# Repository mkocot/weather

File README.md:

# Known ID
0x00 Reserved
0x01 Temerature
0x02 Pressure
0x03 Humidity
0x04 UNUSED (was time)
0x05 Voltage (like in battery power)
0x06 Screen

Packet
name    value   size    note
MAGIC   W       1
Version 1       1
MAC     ?       6
Count   ?       1       Total number of 'sensors' in Packet
Payload ?       ?
Sensor
ID      ?       1       See Known ID
DATA

Most sensors use 4 bytes of data

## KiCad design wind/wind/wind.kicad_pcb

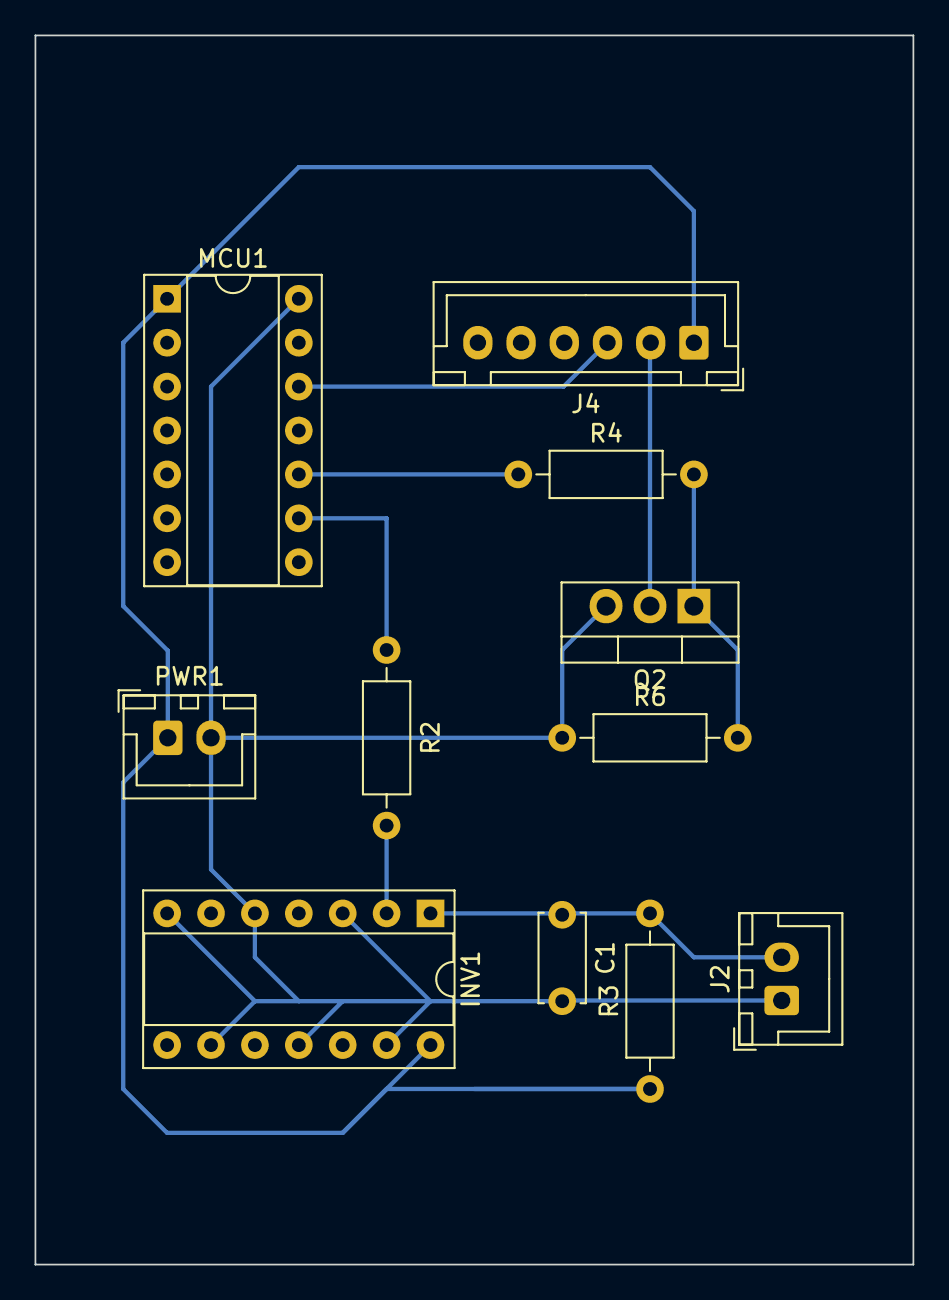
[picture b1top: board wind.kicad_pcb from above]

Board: 2 copper layers, 50.8 x 71.1 mm, 11 parts (0 on the bottom side), 9 nets.

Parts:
C1: 100n; C_Disc_D5.0mm_W2.5mm_P5.00mm
INV1: 74HC14; DIP-14_W7.62mm_Socket
J2: Conn_01x02_Socket; JST_XH_B2B-XH-A_1x02_P2.50mm_Vertical
J4: Conn_01x05_Socket; JST_XH_B6B-XH-A_1x06_P2.50mm_Vertical
MCU1: ATtiny24-20P; DIP-14_W7.62mm_Socket
PWR1: Conn_01x02_Socket; JST_XH_B2B-XH-A_1x02_P2.50mm_Vertical
Q2: IRLZ44N; TO-220-3_Vertical
R2: 1k; R_Axial_DIN0207_L6.3mm_D2.5mm_P10.16mm_Horizontal
R3: 47K; R_Axial_DIN0207_L6.3mm_D2.5mm_P10.16mm_Horizontal
R4: 10k; R_Axial_DIN0207_L6.3mm_D2.5mm_P10.16mm_Horizontal
R6: 56K; R_Axial_DIN0207_L6.3mm_D2.5mm_P10.16mm_Horizontal

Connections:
+3V3: INV1.14 (VCC), J4.1, MCU1.1 (VCC), PWR1.1, R3.1
/RadioController/GND_IN: J4.2, Q2.2 (D)
/RadioController/RADIO_EN: MCU1.10 (PA3), R4.1
/RadioController/Rx: J4.3, MCU1.12 (PA1)
GND: C1.2, INV1.3, INV1.5, INV1.7 (GND), INV1.9, INV1.11, INV1.13, J2.1, MCU1.14 (GND), PWR1.2, Q2.3 (S), R6.1
unnamed: INV1.2, R2.2
unnamed: C1.1, INV1.1, J2.2, R3.2
unnamed: MCU1.9 (PA4), R2.1
unnamed: Q2.1 (G), R4.2, R6.2

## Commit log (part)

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2021-01-13 init
2021-01-13 ignore config.h
2021-01-13 Change source file name
2021-01-16 Add web backend
2021-01-16 Fix (badly) 12h format to 24h
2021-01-18 reformat
2021-01-18 remove unused import
2021-01-18 add server side
2021-01-18 Add auto refresh
2021-01-18 Change default server port
2021-01-18 Add example systemd services
2021-01-20 remove not used code
2021-02-04 Get latest not earliest date
2021-02-08 Filter-out outilers
2021-03-13 Add known id to readme
2021-03-13 Remove unused parsts
2021-03-13 Add more info
2021-03-15 working prototype
2021-03-18 overhaul
2021-03-18 add font
2021-03-18 Dang, we need old python3
2021-03-18 make it old again
2021-03-18 another fixes
2021-03-18 minor fixes
2021-03-18 Fix: invalid device id
2021-03-18 add missing font data
2021-03-18 fix graph
2021-03-18 add draw module...
2021-03-18 quick and dirty server fix
2021-04-12 Weather: Battery optimization
    + Assigned static IP (255.255.255.255/32) rfc6890
    + Disable Serial by default (W_SILENT flag)
    + Disable LED by default (W_BLINK) - it will 'blink' on start anyway,
    this is somehow hardwired
    + UDP: use yield() not delay(2000) after endPacket
    + Add delay after deepSleep ensuring we don't hit loop again
2021-04-12 weather: Change IP
    + Replace 255.255.255.255 with 127.255.255.255. Previous one was causing some odd issues. This address is set only to prevent DHCP requests.
    + Add small delay after yield in UDP, as sometimes packets was not
    received
2021-04-13 Increase delay after finishing UDP to 300ms
    When signal is weak we need more time than 100ms, anyway still better
    than previous 2000
2021-04-13 screen: make it work
2021-05-01 Fix: battery drain on WiFi failure - required RST
2021-05-02 Fix: no data from sensor crash request
2021-06-15 Reuse 'sock' to send data
2021-06-15 Fix: dictionary changed size
2021-06-16 Add 3d cases
2021-06-26 models
2021-06-29 polish case
2021-08-05 Change timers
    * Incrase no network to 5m (from 1m)
    * Increase wait after endPacket to 400ms (from 300ms)
2021-08-05 Clean up #if/#else/#endif
2021-08-05 Tweaked width
2021-08-05 Tweaked graph width
2022-01-23 Add relative Humidity
2022-01-23 fix nulls
2022-08-30 Simply data reader
2022-09-19 rewrite to platformio
2022-09-24 sum changes
2022-09-24 Add another one
2022-09-24 cleanup fetcher
2022-09-24 cleanup weather.py
2022-09-24 add 3rd sensor, ui changes
2022-09-24 disable mqtt, untile fixed
2022-09-26 Restore 0.1 temp resolution
2022-09-26 calculatable time points
2022-09-26 Change time to 24h
2022-09-26 redesign plots
2022-09-29 more asyncio
2022-10-04 POC: OTA + Scheduler
2022-10-04 Change " to '
2022-10-26 quick fix for async
2022-11-04 Use quart as framework
2022-11-04 Increase default storage to 5y
2023-01-06 Add new radio: HC12
2023-01-07 add header to packet, use SPI for sensor
2023-01-07 poc python decoder
2023-01-08 Add new protocol over uart
2023-01-08 parse fixes
2023-01-08 off-by-one (tm)
2023-01-13 Replace outdoor sensor with BME280
2023-01-13 Reduce #if/#elif/#else
2023-01-13 Move W_BSEC flag to config
2023-05-06 wip: add shaky sqlite support for storage
2023-05-06 Update Web UI
2023-05-06 Use new backend for server
2023-05-06 New backend for gather
2023-05-06 fix: store timestamp as number not text
2023-05-06 fix: timestamp added to wrong backend
2023-05-16 select MINimum reported voltage
2024-04-04 Add "tunnel" protocol
2024-04-04 Use HW serial for HC12
2024-04-04 Use older espressif32 to fix iussue with hidden wifi
2024-04-05 Use correct crc8
2024-04-06 Changes to fixed crc8
2024-04-08 Add prototype for wind sensor
2024-05-18 Simplify plots
2024-05-18 Set line type to linear for higher frequency one
2024-06-06 fix: skip interpolating if boundary value is null
2024-06-06 Remove unused console.log
2024-11-04 add pcb project
2025-01-08 Add multi Temp, Hum and Pressure sensor
2025-01-19 New sensor type
2025-01-19 weather_case
2025-01-25 Hacky sending NaN for missing sensors
    This should be fixed one day...
2025-01-25 Read new protocol from sidekick mcu
2025-01-25 Update compound unpack code
2025-01-25 Change presentation
2025-01-26 Early support for multi-sensor of same type
2025-09-19 Add support for smaller packet V2@HC12
2025-09-19 Add support for wind speed and dir
2025-09-24 Support for multiple bind points
2025-09-24 espnow
2025-09-24 fix: args not closuers
2025-09-25 fix: no battery data
2025-12-15 fix: corrected speed/dir function
2025-12-15 hack: filter wind speed
    Sometimes first receiverd value is way too big for unknown reasons.
    If that happens replace it with value of next reading.
